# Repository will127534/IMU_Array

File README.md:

# IMU sensor Array   
Based on 32x ICM-42688-P and ICE40UP5K

## System Block Diagram

Blog post: [https://www.willwhang.dev/Project-IMU-Array/](https://www.willwhang.dev/Project-IMU-Array/)

## Dictionary Structure

* IMUArray_SensorBoard: KiCad files for the Sensor board
* IMUArray_BreakoutBoard: KiCad files for the Sensor breakout board with Raspberry Pi Pico  
* MicroPythonCode: MicroPython code for Raspberry Pi Pico  
* FPGACode: Verilog files for the FPGA

## Notes
The hardware is specifically designed for 6-layer board and as you can see from the photos it is using via-in-pad, though I still need to use smaller via dimensions (0.2mm drill). Gerber, BOM and CPL files are also available. Or you can order it from PCBWay [here](https://www.pcbway.com/project/shareproject/IMU_Array_Sensor_board_84cfc54a.html). (Thank you PCBWay for sponsering this project!)

You can have them populate top side only, the back side are some 0402 decoupling caps that can be easily hand soldered. Do note that the FPC connector is selected because it has the least width, but the plastic latch is way fragile then I though, so becareful.   

As for the breakout board, it is really just for supporting the bring up process, I'm gonna design some other based boards to use this IMU array for my other projects (Geophone replacements).  

The code is still in its early stages so there isn't a lot of "Handy" functions to set different ODR (Sampling rate)/FSR (Full Scale range) and functions, but mostly just hand calculated values for the registers. Rightnow it is set to 200Hz sampling rate with interupt and external 32Khz clock enabled. For the Verilog code, please don't judge, I'm too lazy to save 4096 LUTs for the 512 byte IMU data, I mean for some reason ICE40UP5K is pretty cheap so I might as will to utilized it fully, right?  

Most importantly, the code right now does not do any fancy data processing but only reading out 32x IMU data and either send all of them or do a simple average (accumulating only actually) and output the result (it does handle the 4 different rotations of the IMUs).  

The project is still in developments, and here are the issues:  
1. SPI clock is not stable higher then 5Mhz to the FPGA, work is on-going to move the data shifting posedge from ICE40 internal 48Mhz clock to use SCK directly.  
    UPDATE on 2024/08/04 - This has been resolved, now I can run the SPI at 20Mhz.
2. Currently it is not possible to send out all IMU data at 200Hz, but only the averaged value. The bottleneck is in microPython code to print out the data to USB-CDC.  
   UPDATE on 2024/08/04 - Overclocked to 250Mhz so I can send out 100Hz x32 IMUs data to PC, so the focus now is the algorithm to filter out data.

## Footnotes

ICE40 micropython/circuitpython upload code from:   
https://github.com/skerr92/Oakdevtech_CircuitPython_IcePython  
Which is actually designed for the IcyBlue FPGA Feather board (ICE40 + RP2040 on a Feather board)   
https://www.tindie.com/products/oakdevtech/icyblue-fpga-feather-v2/  

[Interactive BOM](https://htmlpreview.github.io/?https://github.com/will127534/IMU_Array/blob/main/IMUArray_SensorBoard/bom/ibom.html) [(provided by InteractiveHtmlBom)
](https://github.com/openscopeproject/InteractiveHtmlBom) 

Papers and Inspirations:  
1. The inspirations comes from Sony's crazy 16x IMU array board for SPRESENSE, which is so powerfull that is it export controlled.   

https://monoist.itmedia.co.jp/mn/articles/2404/26/news134.html

2. Kamata, Hiroyuki et al. “MEMS Gyro Array Employing Array Signal Processing for Interference and Outlier Suppression.” 2020 IEEE International Symposium on Inertial Sensors and Systems (INERTIAL) (2020): 1-4. 
https://ieeexplore.ieee.org/document/9090089   
https://www.kenkai.jaxa.jp/research/innovation/multi_imu.html  
https://www.sony.com/ja/SonyInfo/technology/stories/entries/Spresense/  
This is also what Sony's IMU array board is based of I think.

3. Blocher, Lukas et al. “Purely Inertial Navigation with a Low-Cost MEMS Sensor Array.” 2021 IEEE International Symposium on Inertial Sensors and Systems (INERTIAL) (2021): 1-4.
https://ieeexplore.ieee.org/document/9430468

5. Wang, Liqiang et al. “Improving the Navigation Performance of the MEMS IMU Array by Precise Calibration.” IEEE Sensors Journal 21 (2021): 26050-26058.
http://i2nav.com/ueditor/jsp/upload/file/20221125/1669361019644065348.pdf

6. Nilsson, John-Olof et al. “Aligning the Forces—Eliminating the Misalignments in IMU Arrays.” IEEE Transactions on Instrumentation and Measurement 63 (2014): 2498-2500.
https://ieeexplore.ieee.org/document/6879287

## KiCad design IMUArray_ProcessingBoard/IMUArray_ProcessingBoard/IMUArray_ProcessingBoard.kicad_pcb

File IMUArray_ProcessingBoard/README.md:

# IMU Array Data Processing Board

Here is the board and code for the processing board I'm designing mainly for my geophone replacement project.

## System Block Diagram

## Dictionary Structure

* IMUArray_ProcessingBoard: KiCad files for the board
* Code: C Code for the board

## Hardware Notes

So, long story short, this is essentially a custom-built Pico W using the same RP2040 + CYW43439 (Type 1YN) combo. Additionally, the crystal for the RP2040 was replaced with a VCTCXO, allowing me to tune the onboard clock to match the GPS clock (i.e., GPSDO). The code supports both NTP and GPS+PPS as time sync sources. The main reason for this is that I’m using the same crystal to send a stable 32kHz signal to the IMU array.

You might ask, why on earth do I have a full bridge rectifier along with a high-voltage DC-DC step-down converter? This was mainly because I initially intended to use my doorbell system (24V AC) to power the system. I kind of regret this decision, so it was removed in v2.0 (I’m waiting for the board to arrive).

Furthermore, I originally planned to rely on Wi-Fi to transmit the data, so the USB connector (JST-SH) wasn’t designed for external connection but only for programming. See more on the blog post. However, I ended up deciding to make the USB accessible from the case in the future v2.0 design.

## Software Notes

In the code folder, you’ll find two files. The goal for `imu_simple` is to have a much simpler codebase, so two years later, I can still understand what’s going on or easily test new ideas. `imu_main` is the main code I’m currently using, which follows the structure outlined below:

The data can be sent via either TCP or USB. If a client connects to the TCP server, it will switch to sending data through TCP. During startup, and once per hour, the system performs an NTP time sync. If GPS is available, it also uses it to calculate the UNIX timestamp offset from the internal system clock. As a result, each IMU sample contains not only the timestamp from the IMU itself but also a UNIX timestamp. However, note that these two timestamps are not strongly related (since the GPSDO requires time to adjust the error).

For IMU data processing, the code uses the method described in Reference 6 to calibrate the IMU array. Refer to the MATLAB code section for generating imu_cal.h. The data processing applies the calibration and merges the 32 IMU data into one dataset. The RP2040 is surprisingly fast enough to handle all of this using floating-point operations, even without hardware FPU, and can run at up to 500Hz. A side note here is that to measure the processing time, I placed the data processing code along with the SPI read function. By measuring the CS pin, I can determine the total time spent on both data acquisition and processing. The 500Hz rate accounts for both tasks in sequence, not in parallel (i.e., I’m not using both CPU cores for reading and processing, but instead for reading/processing and Wi-Fi/Bluetooth data processing).

Lastly, I’m not entirely sure how to share the code I wrote under the RP2040 SDK’s pico-example folder, so you may need to figure out how to set up the build environment outside of the SDK. Also, please let me know how to share it if you have suggestions.

## Footnotes

[Interactive BOM](https://htmlpreview.github.io/?https://github.com/will127534/IMU_Array/blob/main/IMUArray_ProcessingBoard/IMUArray_ProcessingBoard/bom/ibom.html) [(provided by InteractiveHtmlBom)
](https://github.com/openscopeproject/InteractiveHtmlBom) 

PIO input capture code from: https://people.ece.cornell.edu/land/courses/ece4760/RP2040/C_SDK_PIO_control/Input_capture/index_pio_control.html

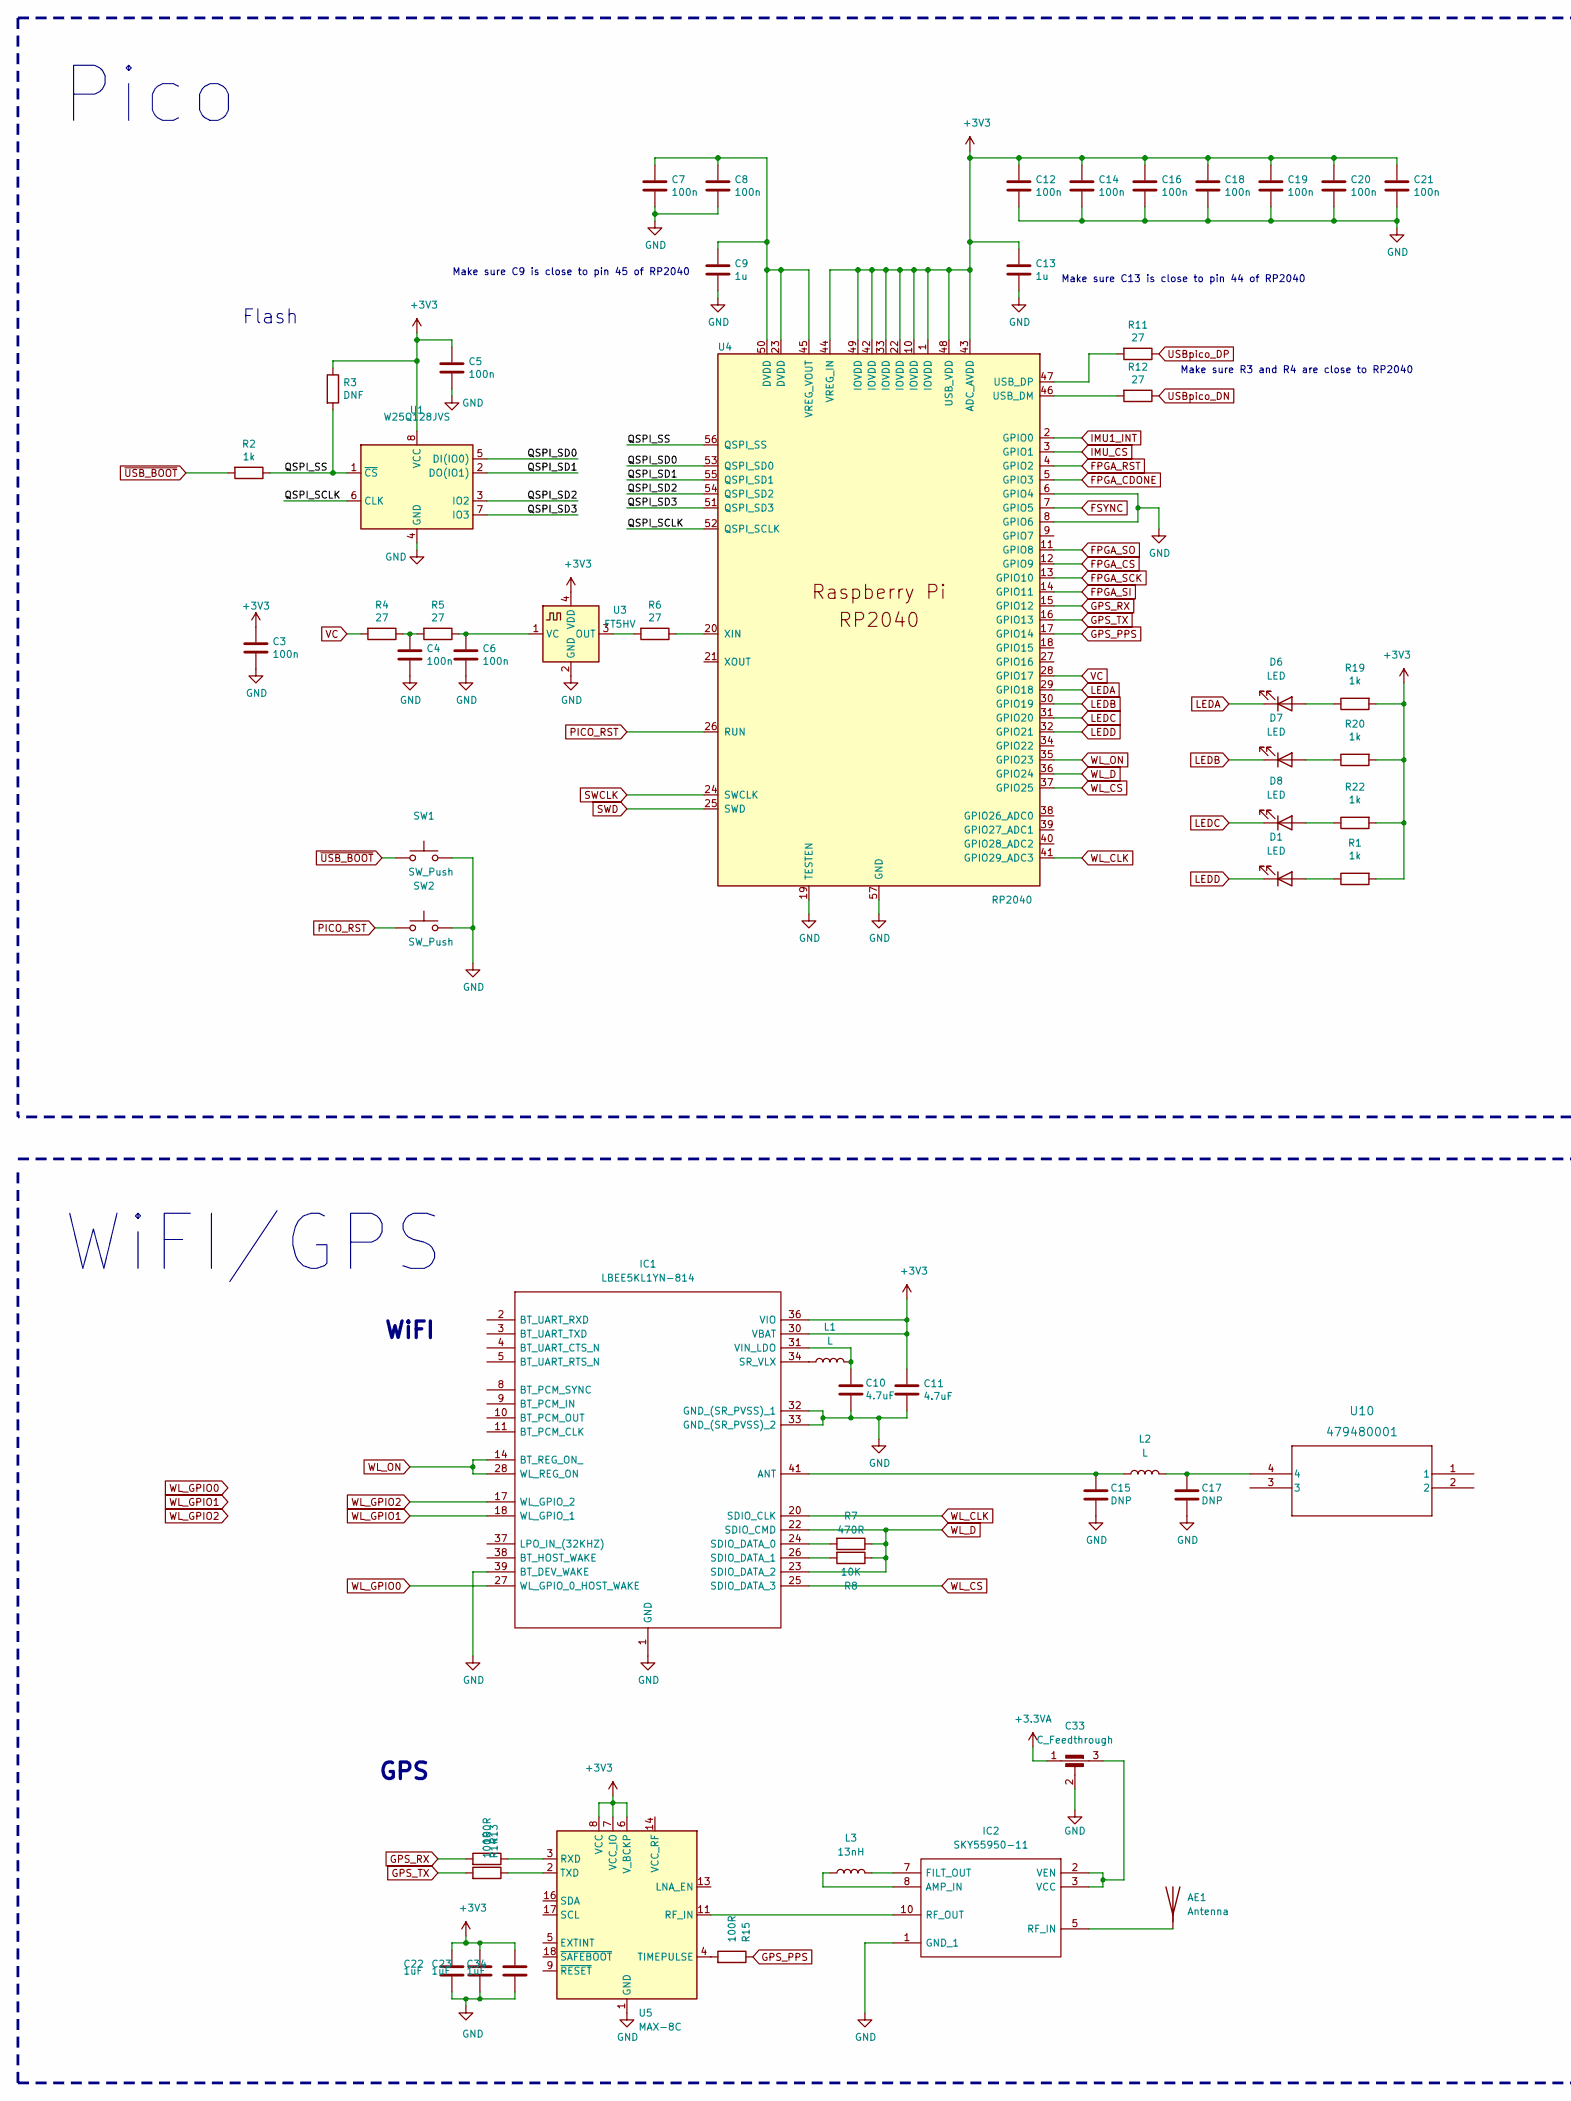
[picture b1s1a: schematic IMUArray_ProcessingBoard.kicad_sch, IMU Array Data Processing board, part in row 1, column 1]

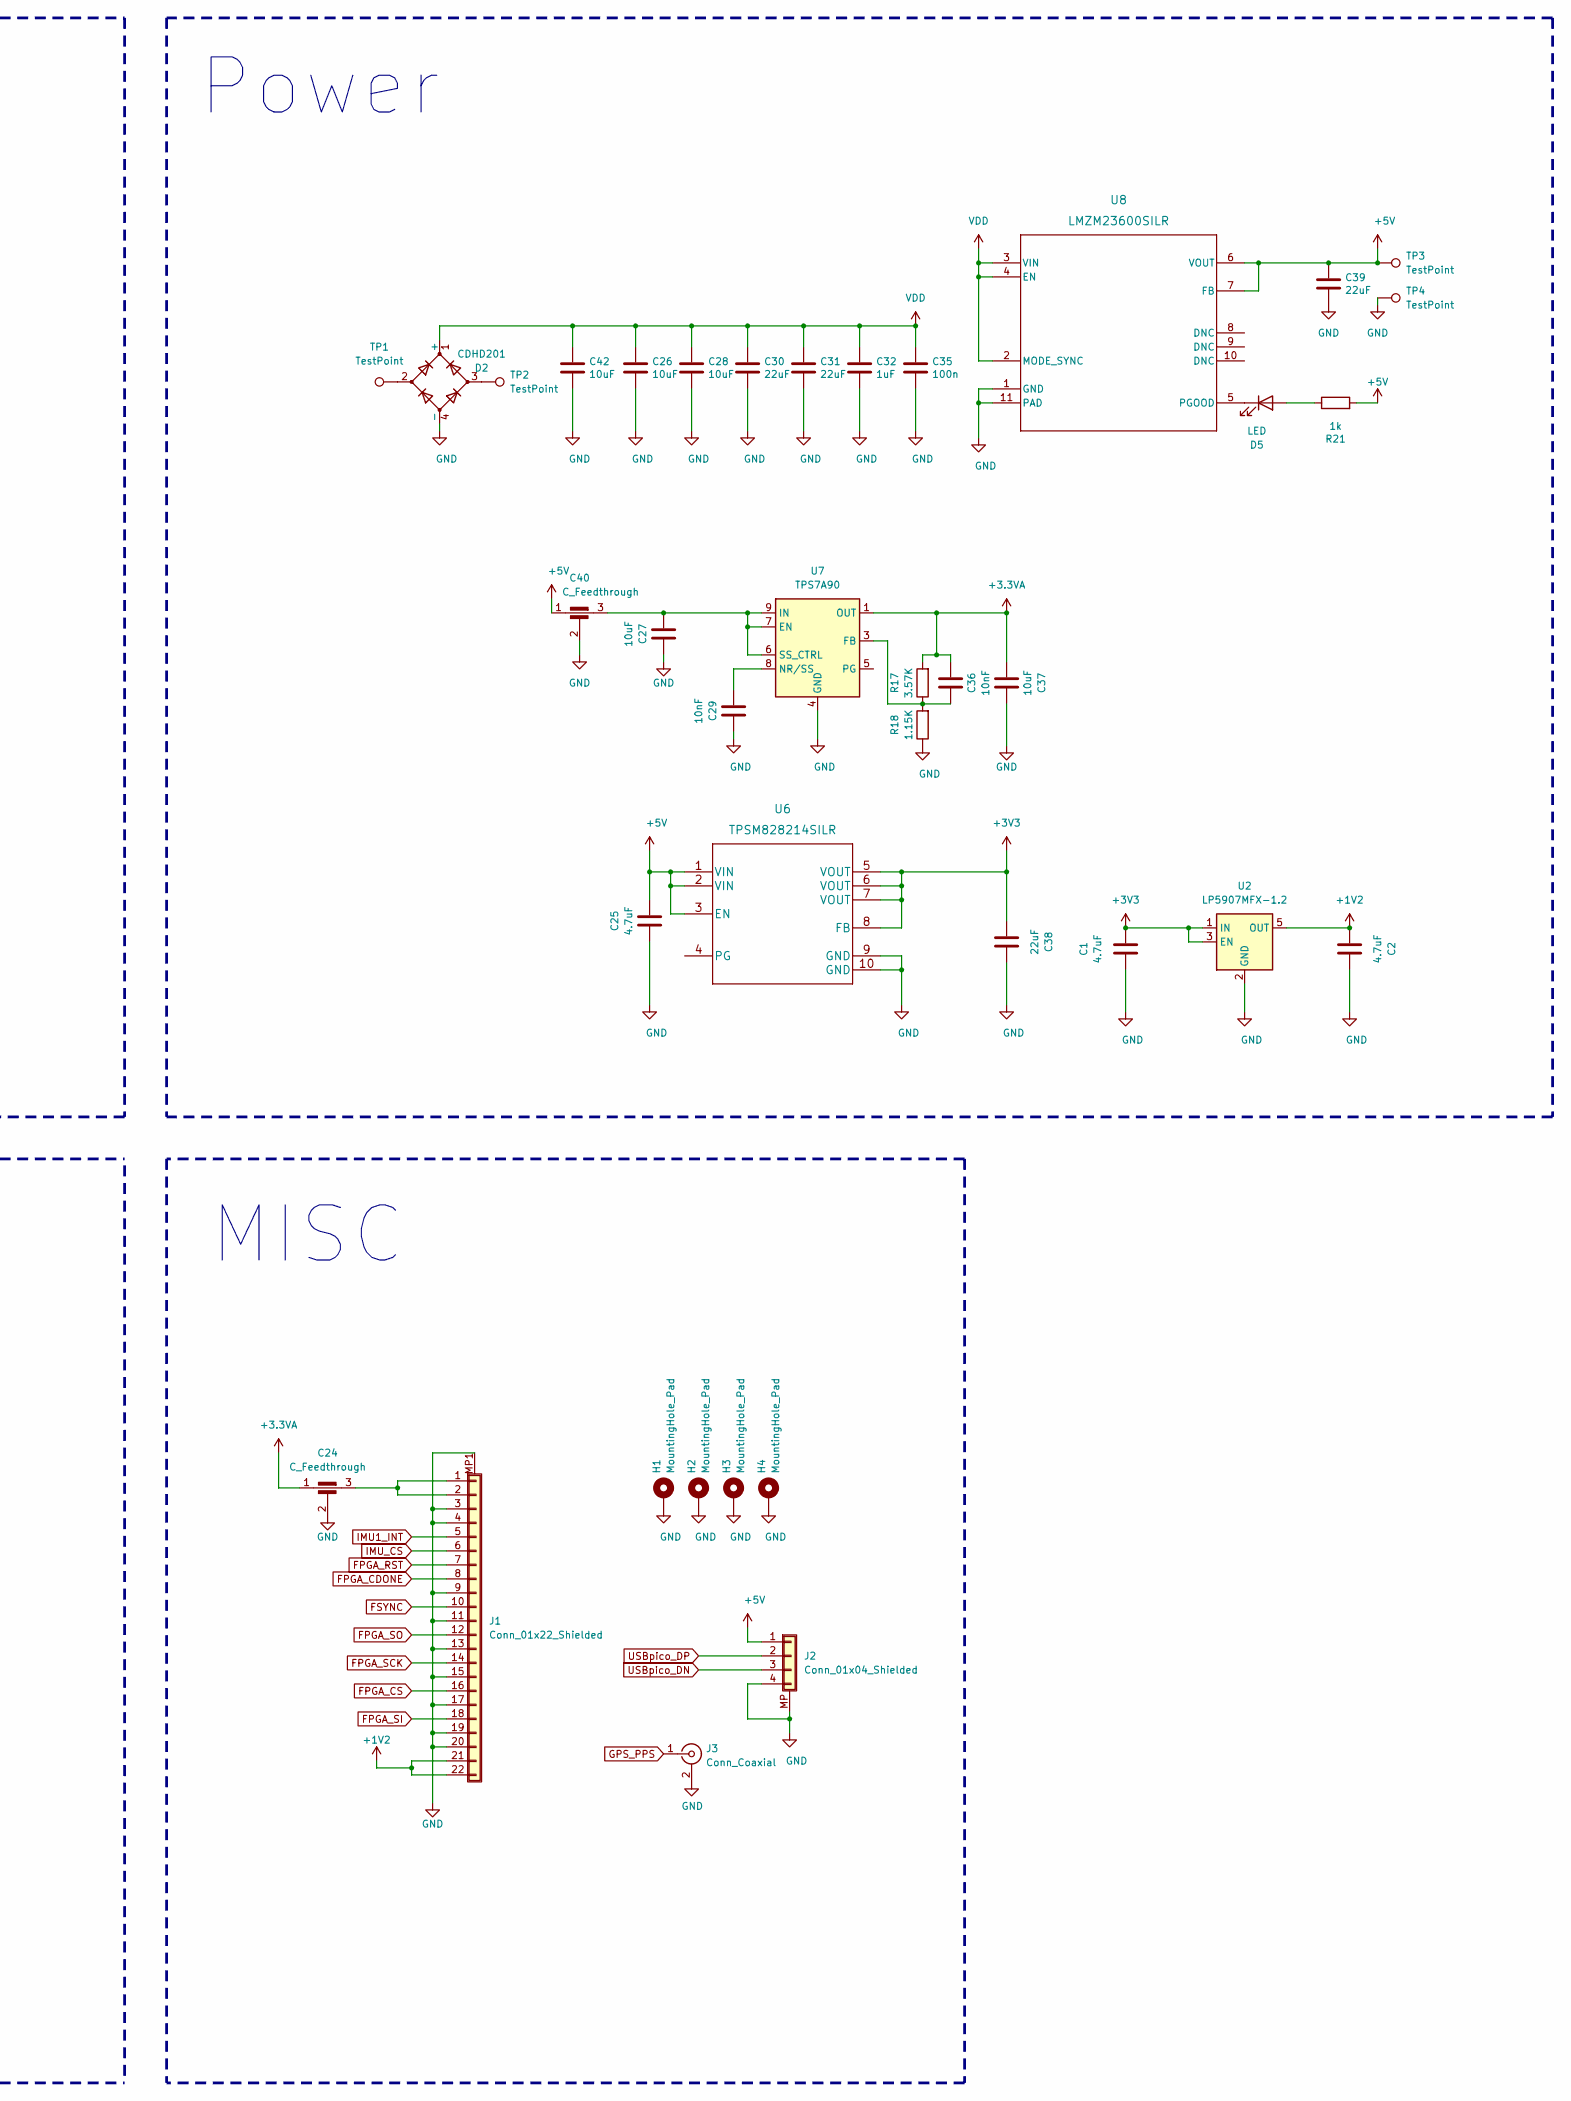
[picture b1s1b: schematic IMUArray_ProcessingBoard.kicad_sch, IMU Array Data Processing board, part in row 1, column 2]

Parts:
AE1: Antenna; APAES1575R1040J34-T_ABR
C1, C2: 4.7uF; C_0603_1608Metric
C3, C4, C5, C6, C7, C8, C12, C14, C16, C18, C19, C20, C21: 100n; C_0402_1005Metric
C9, C13: 1u; C_0402_1005Metric
C10, C11: 4.7uF; C_0402_1005Metric
C15, C17: DNP; C_0402_1005Metric
C22, C23, C34: 1uF; C_0402_1005Metric
C24, C33, C40: C_Feedthrough; NFM18CC101R1C3D
C25: 4.7uF; C_0805_2012Metric
C26, C28, C42: 10uF; C_1206_3216Metric
C27, C37: 10uF; C_0603_1608Metric
C29, C36: 10nF; C_0402_1005Metric
C30, C31: 22uF; C_1206_3216Metric
C32: 1uF; C_0603_1608Metric
C35: 100n; C_0603_1608Metric
C38, C39: 22uF; C_0805_2012Metric
D1, D5, D6, D7, D8: LED; LED_0603_1608Metric
D2: CDHD201
H1, H2, H3, H4: MountingHole_Pad; MountingHole_3.2mm_M3_Pad
IC1: LBEE5KL1YN-814; LBEE5KL1YN814; Mouser Part Number 81-LBEE5KL1YN-814
IC2: SKY55950-11; SKY5595011; Mouser Part Number 873-SKY55950-11
J1: Conn_01x22_Shielded; Hirose_FH12-22S-0.5SH_1x22-1MP_P0.50mm_Horizontal
J2: Conn_01x04_Shielded; JST_SH_BM04B-SRSS-TB_1x04-1MP_P1.00mm_Vertical
J3: Conn_Coaxial; U.FL_Hirose_U.FL-R-SMT-1_Vertical
L1: L; L_0603_1608Metric
L2: L; L_0402_1005Metric
L3: 13nH; L_0402_1005Metric
R1, R2, R19, R20, R21, R22: 1k; C_0402_1005Metric
R3: DNF; C_0402_1005Metric
R4, R5, R6, R11, R12: 27; C_0402_1005Metric
R7: 470R; C_0402_1005Metric
R8: 10K; C_0402_1005Metric
R13, R14, R15: 100R; R_0402_1005Metric
R17: 3.57K; R_0402_1005Metric
R18: 1.15K; R_0402_1005Metric
SW1, SW2: SW_Push; SW_Push_SPST_NO_Alps_SKRK
TP1, TP2, TP3, TP4: TestPoint; TestPoint_Pad_D2.0mm
U1: W25Q128JVS; DFN-8-1EP_3x2mm_P0.5mm_EP1.36x1.46mm
U2: LP5907MFX-1.2; SOT-23-5
U3: FT5HV; Oscillator_SMD_SeikoEpson_SG8002CE-4Pin_3.2x2.5mm
U4: RP2040; RP2040-QFN-56
U5: MAX-8C; ublox_MAX
U6: TPSM828214SILR; TPSM82821SILR
U7: TPS7A90; Texas_S-PDSO-N10_EP1.2x2mm
U8: LMZM23600SILR; SIL0010A
U10: 479480001; ANT_47948-0001_MOL

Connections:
+1V2: C2.1, J1.21, J1.22, U2.5 (OUT)
+3.3VA: C24.1, C33.1, C36.2, C37.1, R17.2, U7.1 (OUT), U7.2 (OUT)
+3V3: C1.2, C3.1, C5.1, C11.1, C12.1, C13.1, C14.1, C16.1, C18.1, C19.1, C20.1, C21.1, C22.1, C23.1, C34.1, C38.1, IC1.30 (VBAT), IC1.36 (VIO), R1.2, R3.1, R19.2, R20.2, R22.2, U1.8 (VCC), U2.1 (IN), U2.3 (EN), U3.4 (VDD), U4.1 (IOVDD), U4.10 (IOVDD), U4.22 (IOVDD), U4.33 (IOVDD), U4.42 (IOVDD), U4.43 (ADC_AVDD), U4.44 (VREG_IN), U4.48 (USB_VDD), U4.49 (IOVDD), U5.6 (V_BCKP), U5.7 (VCC_IO), U5.8 (VCC), U6.5 (VOUT), U6.6 (VOUT), U6.7 (VOUT), U6.8 (FB)
+5V: C25.2, C39.1, C40.1, J2.1, R21.2, TP3.1, U6.1 (VIN), U6.2 (VIN), U6.3 (EN), U8.6 (VOUT), U8.7 (FB)
/QSPI_SCLK: U1.6 (CLK), U4.52 (QSPI_SCLK)
/QSPI_SD0: U1.5 (DI(IO0)), U4.53 (QSPI_SD0)
/QSPI_SD1: U1.2 (DO(IO1)), U4.55 (QSPI_SD1)
/QSPI_SD2: U1.3 (IO2), U4.54 (QSPI_SD2)
/QSPI_SD3: U1.7 (IO3), U4.51 (QSPI_SD3)
/QSPI_SS: R2.1, R3.2, U1.1 (~CS), U4.56 (QSPI_SS)
FPGA_CDONE: J1.8, U4.5 (GPIO3)
FPGA_CS: J1.16, U4.12 (GPIO9)
FPGA_RST: J1.7, U4.4 (GPIO2)
FPGA_SCK: J1.14, U4.13 (GPIO10)
FPGA_SI: J1.18, U4.14 (GPIO11)
FPGA_SO: J1.12, U4.11 (GPIO8)
FSYNC: J1.10, U4.7 (GPIO5)
GND: C1.1, C2.2, C3.2, C4.2, C5.2, C6.2, C7.2, C8.2, C9.2, C10.2, C11.2, C12.2, C13.2, C14.2, C15.2, C16.2, C17.2, C18.2, C19.2, C20.2, C21.2, C22.2, C23.2, C24.2, C25.1, C26.2, C27.2, C28.2, C29.2, C30.2, C31.2, C32.2, C33.2, C34.2, C35.2, C37.2, C38.2, C39.2, C40.2, C42.2, D2.4 (-), H1.1, H2.1, H3.1, H4.1, IC1.1 (GND), IC1.12 (GND_2), IC1.19 (GND_3), IC1.21 (GND_4), IC1.29 (GND_5), IC1.32 (GND_(SR_PVSS)_1), IC1.33 (GND_(SR_PVSS)_2), IC1.35 (GND_6), IC1.39 (BT_DEV_WAKE), IC1.40 (GND_7), IC1.42 (GND_8), IC1.43 (GND_9), IC1.44 (GND_10), IC1.45 (GND_11), IC1.46 (GND_12), IC2.1 (GND_1), IC2.4 (GND_2), IC2.6 (GND_3), IC2.9 (GND_4), IC2.11 (GND_5), J1.3, J1.4, J1.9, J1.11, J1.13, J1.15, J1.17, J1.19, J1.20, J1.MP1 (Shield), J1.MP2 (Shield), J2.4, J2.MP (Shield), J3.2 (Ext), R18.1, SW1.2, SW2.2, TP4.1, U1.4 (GND), U2.2 (GND), U3.2 (GND), U4.6 (GPIO4), U4.8 (GPIO6), U4.19 (TESTEN), U4.57 (GND), U5.1 (GND), U5.10 (GND), U5.12 (GND), U6.9 (GND), U6.10 (GND), U7.4 (GND), U7.11 (GND), U8.1 (GND), U8.11 (PAD)
GPS_PPS: J3.1 (In), R15.1, U4.17 (GPIO14)
GPS_RX: R13.2, U4.15 (GPIO12)
GPS_TX: R14.2, U4.16 (GPIO13)
IMU1_INT: J1.5, U4.2 (GPIO0)
IMU_CS: J1.6, U4.3 (GPIO1)
LEDA: D6.1 (K), U4.29 (GPIO18)
LEDB: D7.1 (K), U4.30 (GPIO19)
LEDC: D8.1 (K), U4.31 (GPIO20)
LEDD: D1.1 (K), U4.32 (GPIO21)
unnamed: AE1.1 (A), IC2.5 (RF_IN)
unnamed: C4.1, R4.1, R5.2
unnamed: C17.1, L2.2, U10.4
unnamed: D1.2 (A), R1.1
unnamed: D2.2, TP1.1
unnamed: D2.3, TP2.1
unnamed: D5.2 (A), R21.1
unnamed: D5.1 (K), U8.5 (PGOOD)
unnamed: D6.2 (A), R19.1
unnamed: D7.2 (A), R20.1
unnamed: D8.2 (A), R22.1
unnamed: C15.1, IC1.41 (ANT), L2.1
unnamed: IC1.24 (SDIO_DATA_0), R7.2
unnamed: IC1.26 (SDIO_DATA_1), R8.2
unnamed: IC1.34 (SR_VLX), L1.1
unnamed: C10.1, IC1.31 (VIN_LDO), L1.2
unnamed: IC2.8 (AMP_IN), L3.1
unnamed: IC2.7 (FILT_OUT), L3.2
unnamed: IC2.10 (RF_OUT), U5.11 (RF_IN)
unnamed: C33.3, IC2.2 (VEN), IC2.3 (VCC)
unnamed: C24.3, J1.1, J1.2
unnamed: R6.2, U3.3 (OUT)
unnamed: C6.1, R5.1, U3.1 (VC)
unnamed: R12.2, U4.46 (USB_DM)
unnamed: R11.2, U4.47 (USB_DP)
unnamed: C7.1, C8.1, C9.1, U4.23 (DVDD), U4.45 (VREG_VOUT), U4.50 (DVDD)
unnamed: R6.1, U4.20 (XIN)
unnamed: R13.1, U5.3 (RXD)
unnamed: R15.2, U5.4 (TIMEPULSE)
unnamed: R14.1, U5.2 (TXD)
unnamed: C27.1, C40.3, U7.6 (SS_CTRL), U7.7 (EN), U7.9 (IN), U7.10 (IN)
unnamed: C36.1, R17.1, R18.2, U7.3 (FB)
unnamed: C29.1, U7.8 (NR/SS)
PICO_RST: SW2.1, U4.26 (RUN)
SWCLK: U4.24 (SWCLK)
SWD: U4.25 (SWD)
USBpico_DN: J2.3, R12.1
USBpico_DP: J2.2, R11.1
VC: R4.2, U4.28 (GPIO17)
VDD: C26.1, C28.1, C30.1, C31.1, C32.1, C35.1, C42.1, D2.1 (+), U8.2 (MODE_SYNC), U8.3 (VIN), U8.4 (EN)
WL_CLK: IC1.20 (SDIO_CLK), U4.41 (GPIO29_ADC3)
WL_CS: IC1.25 (SDIO_DATA_3), U4.37 (GPIO25)
WL_D: IC1.22 (SDIO_CMD), IC1.23 (SDIO_DATA_2), R7.1, R8.1, U4.36 (GPIO24)
WL_GPIO0: IC1.27 (WL_GPIO_0_HOST_WAKE)
WL_GPIO1: IC1.18 (WL_GPIO_1)
WL_GPIO2: IC1.17 (WL_GPIO_2)
WL_ON: IC1.14 (BT_REG_ON_), IC1.28 (WL_REG_ON), U4.35 (GPIO23)
~USB_BOOT: R2.2, SW1.1

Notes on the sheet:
WiFI
Make sure R3 and R4 are close to RP2040
GPS
Make sure C9 is close to pin 45 of RP2040
Power
MISC
WiFI/GPS
Make sure C13 is close to pin 44 of RP2040
Pico
Flash

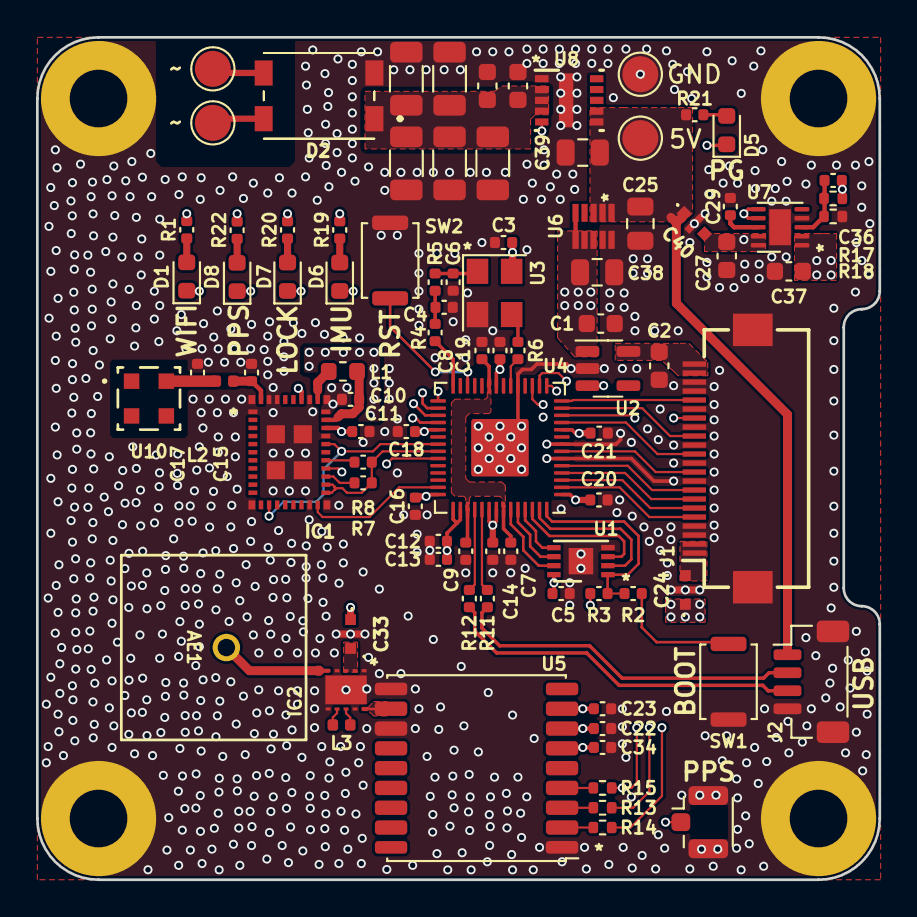
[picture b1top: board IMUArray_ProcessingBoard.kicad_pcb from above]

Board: 4 copper layers, 46.8 x 46.8 mm, 94 parts (0 on the bottom side), 70 nets.

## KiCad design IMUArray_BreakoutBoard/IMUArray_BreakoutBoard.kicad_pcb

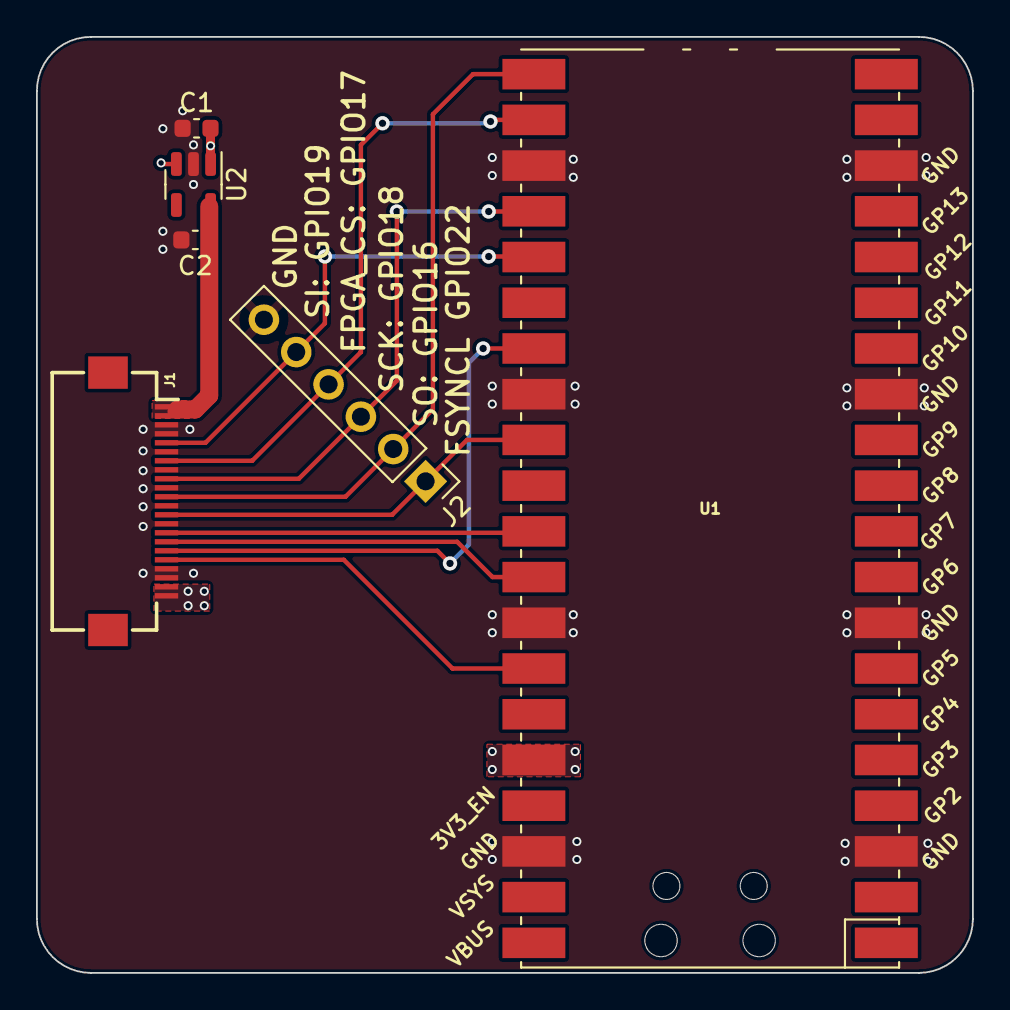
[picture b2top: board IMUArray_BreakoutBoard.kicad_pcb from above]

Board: 4 copper layers, 52.0 x 52.0 mm, 6 parts (0 on the bottom side), 12 nets.

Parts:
C1, C2: 4.7uF; C_0603_1608Metric
J1: Conn_01x22_Shielded; Hirose_FH12-22S-0.5SH_1x22-1MP_P0.50mm_Horizontal
J2: Conn_01x06; PinHeader_1x06_P2.54mm_Vertical
U1: Pico; RPi_Pico_SMD_TH
U2: LP5907MFX-1.2; SOT-23-5

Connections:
+1V2: C2.1, J1.1, J1.2, U2.5 (OUT)
+3V3: C1.2, J1.21, J1.22, U1.36 (3V3), U2.1 (IN), U2.3 (EN)
FPGA_CDONE: J1.15, U1.31 (GPIO26_ADC0)
FPGA_CS: J1.7, J2.4, U1.22 (GPIO17)
FPGA_RST: J1.16, U1.32 (GPIO27_ADC1)
FPGA_SCK: J1.9, J2.3, U1.24 (GPIO18)
FPGA_SI: J1.5, J2.5, U1.25 (GPIO19)
FPGA_SO: J1.11, J2.2, U1.21 (GPIO16)
FSYNC: J1.13, J2.1, U1.29 (GPIO22)
GND: C1.1, C2.2, J1.3, J1.4, J1.6, J1.8, J1.10, J1.12, J1.14, J1.19, J1.20, J2.6, U1.3 (GND), U1.8 (GND), U1.13 (GND), U1.18 (GND), U1.23 (GND), U1.28 (GND), U1.33 (AGND), U1.38 (GND), U2.2 (GND)
IMU1_INT: J1.18, U1.34 (GPIO28_ADC2)
IMU_CS: J1.17, U1.27 (GPIO21)

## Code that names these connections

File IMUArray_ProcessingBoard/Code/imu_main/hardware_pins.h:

#ifndef HARDWARE_PINS_H
#define HARDWARE_PINS_H

// GPIO Pin Definitions
#define IMU_INT 0
#define IMU_CS 1
#define FPGA_RST 2
#define FPGA_CDONE 3
#define FSYNC 5
#define FPGA_RX 8
#define FPGA_CS 9
#define FPGA_SCK 10
#define FPGA_TX 11
#define GPS_RX 12
#define GPS_TX 13
#define GPS_PPS 14
#define VC 17
#define LED_IMU 18
#define LED_LOCK 19
#define LED_PPS 20
#define LED_WIFI 21

#endif // HARDWARE_PINS_H

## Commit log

2024-07-28 init
2024-08-01 Update FPGA SPI code + testbench code
2024-08-01 Add note to run testbench otherwise I will forget in 2 years
2024-08-02 Adding dataset and matlab code to record and analyze
2024-08-02 Update code
2024-10-19 Adding IMU processing board v1.0 and its code
2024-10-19 Adding calibration code
2024-11-04 Update README.md
    Update reference format, add blog post link

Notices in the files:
parts and their libraries:
Copyright 2016 Accelerated Designs. All rights reserved.
